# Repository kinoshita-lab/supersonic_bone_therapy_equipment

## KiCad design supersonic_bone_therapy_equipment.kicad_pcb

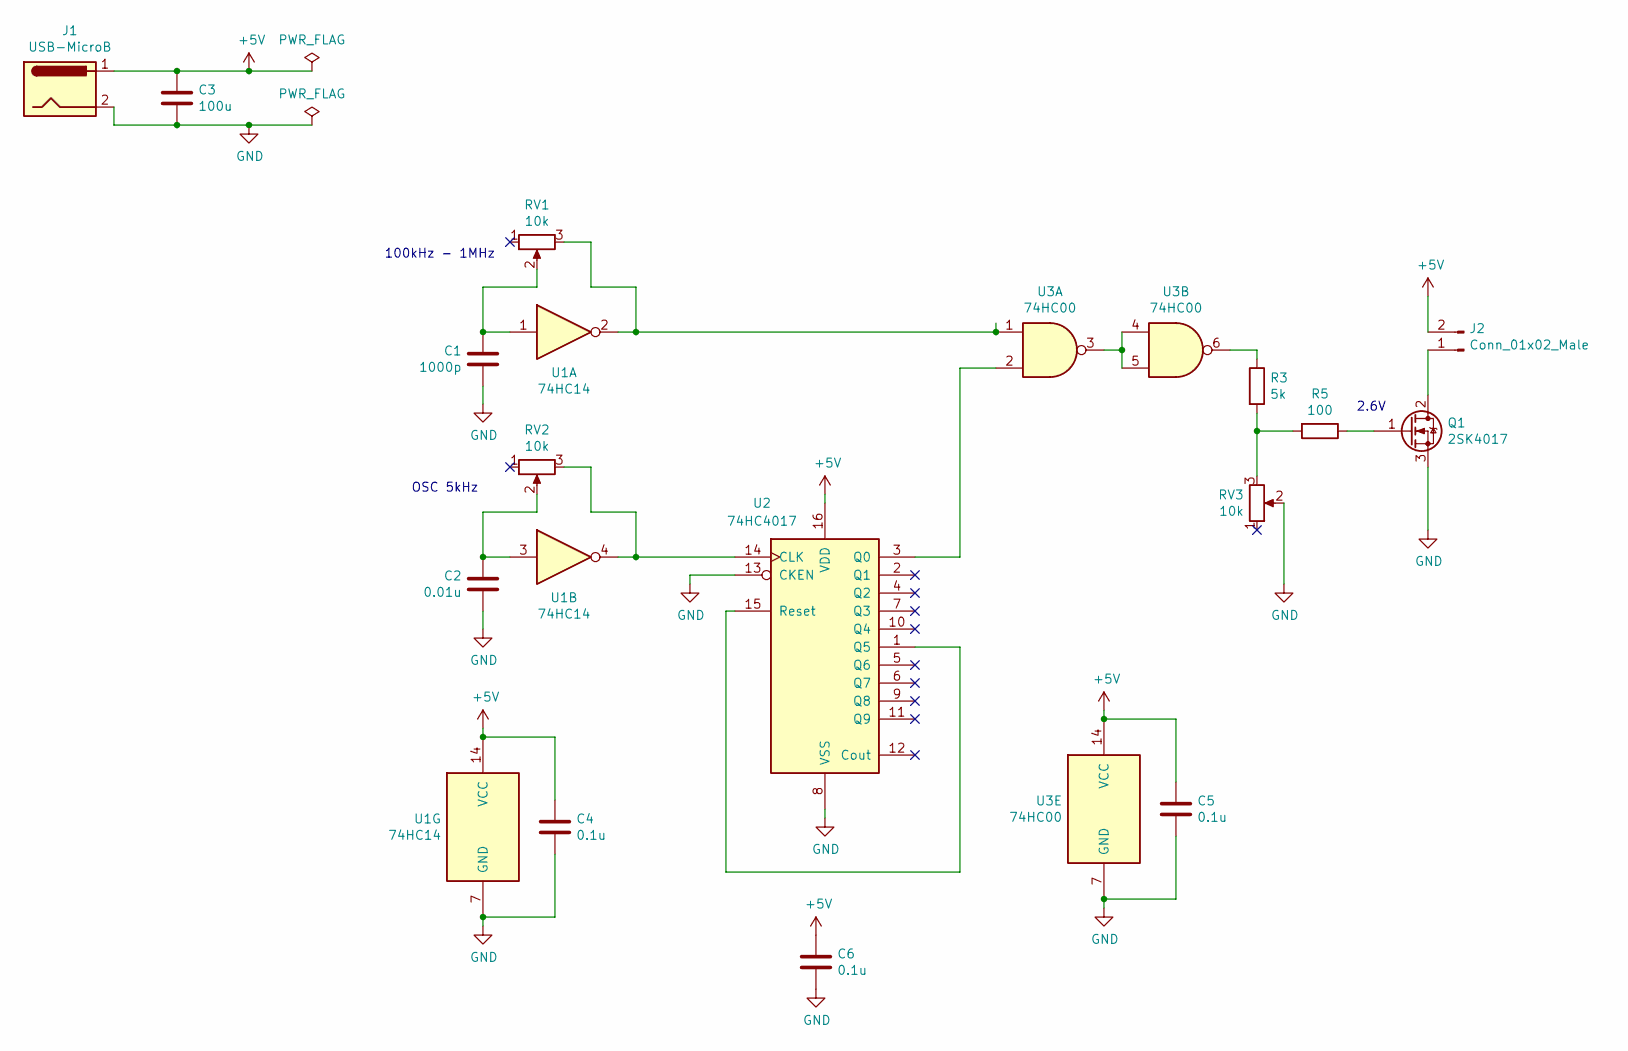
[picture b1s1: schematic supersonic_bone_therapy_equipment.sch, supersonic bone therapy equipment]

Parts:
C1: 1000p; C_0603_HandSoldering
C2: 0.01u; C_0603_HandSoldering
C3: 100u; C_1206_HandSoldering
C4, C5, C6: 0.1u; C_0603_HandSoldering
J1: USB-MicroB; MRUSB-2B-D14NI-S306
J2: Conn_01x02_Male; JST_XH_B02B-XH-A_02x2.50mm_Straight
Q1: 2SK4017; TO-220-3_Vertical
R3: 5k; R_0603_HandSoldering
R5: 100; R_0603_HandSoldering
RV1, RV2, RV3: 10k; Potentiometer_Trimmer-EVM3E
U1: 74HC14; SOIC-14_3.9x8.7mm_Pitch1.27mm
U2: 74HC4017; SOIC-16_3.9x9.9mm_Pitch1.27mm
U3: 74HC00; SOIC-14_3.9x8.7mm_Pitch1.27mm

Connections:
+5V: C3.1, C4.1, C5.1, C6.1, J1.1, J2.2, U1.14 (VCC), U2.16 (VDD), U3.14 (VCC)
GND: C1.2, C2.2, C3.2, C4.2, C5.2, C6.2, J1.2, Q1.3 (S), RV3.2, U1.7 (GND), U2.8 (VSS), U2.13 (CKEN), U3.7 (GND)
unnamed: C1.1, RV1.2, U1.1
unnamed: C2.1, RV2.2, U1.3
unnamed: J2.1, Q1.2 (D)
unnamed: Q1.1 (G), R5.1
unnamed: R3.1, U3.6
unnamed: R3.2, R5.2, RV3.3
unnamed: RV1.3, U1.2, U3.1
unnamed: RV2.3, U1.4, U2.14 (CLK)
unnamed: U2.1 (Q5), U2.15 (Reset)
unnamed: U2.3 (Q0), U3.2
unnamed: U3.3, U3.4, U3.5

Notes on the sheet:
100kHz - 1MHz
OSC 5kHz
2.6V

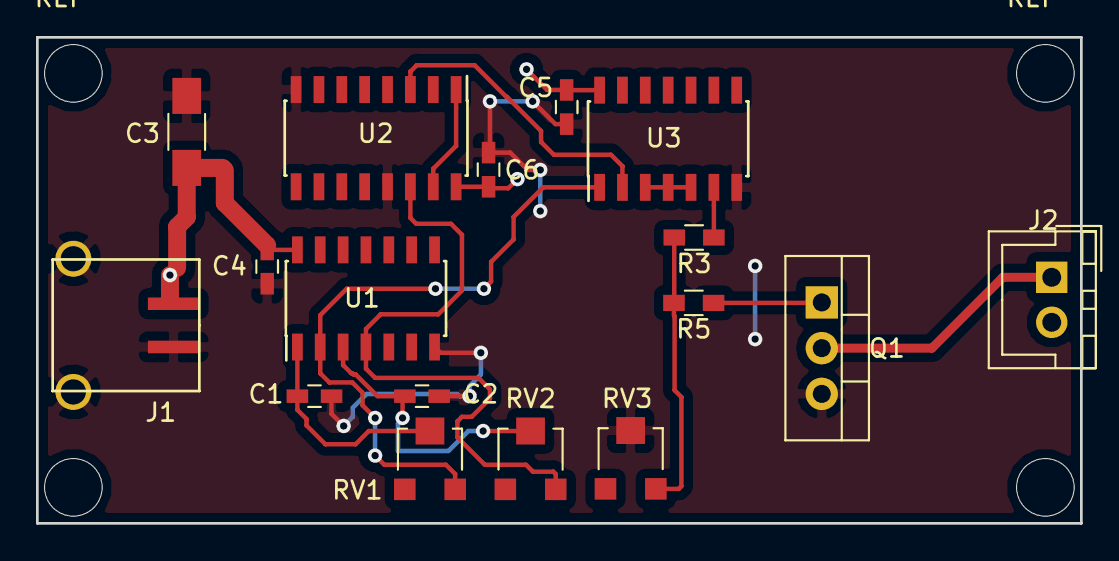
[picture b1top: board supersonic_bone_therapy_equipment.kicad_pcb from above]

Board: 2 copper layers, 58.0 x 27.0 mm, 17 parts (0 on the bottom side), 13 nets.

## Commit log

2019-03-20 initial design
2019-03-20 add pdf
2019-03-20 rotate pdf
